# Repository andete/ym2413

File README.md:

ym2413
======

openMSX YM2413 reverse engineering project

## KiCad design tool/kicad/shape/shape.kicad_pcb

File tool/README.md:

Edit the efm32gg332f1024_pinout.edc file with simplicity studio.

Find it here: http://community.silabs.com/t5/Simplicity-Studio-and-Software/Simplicity-Studio-1-20-energyAware-Tools-OSX-Linux/m-p/107821#M8497

Download the GCC toolchain from:

https://launchpad.net/gcc-arm-embedded/+download

and set the LINUXCS environment var to point to it.

see also: 

http://joost.damad.be/2013/11/using-efm32-simplicitystudio-under-linux.html

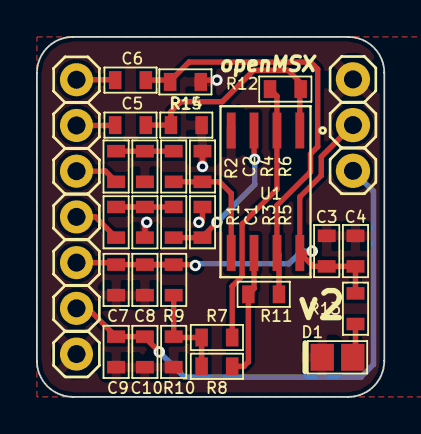
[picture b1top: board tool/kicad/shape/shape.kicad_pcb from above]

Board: 2 copper layers, 19.3 x 20.0 mm, 29 parts (0 on the bottom side), 17 nets.

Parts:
C1, C2: 2.2nF; 0603_S
C3: 0.1uF; 0603_S
C4, C7, C9: 1uF; 0603_S
C5, C6: 0Ohm; 0603_S
C8, C10: 1nF; 0603_S
D1: LED; 0805_LED
K1: CONN_3; PIN_1X3
P1: CONN_7; PIN_1X7_S
R1, R2: 0/2.2k; 0603_S_R
R3, R4, R7, R8: 68k; 0603_S_R
R5, R6, R11, R12: 100k; 0603_S_R
R9: 1.5k; 0603_S_R
R10: 1.21k; 0603_S_R
R13: 3k3; 0603_S_R
R14, R15: NC; 0603_S_R
U1: MCP6022; ATMEL_SO8

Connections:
+3.3V: C9.2, C10.2, K1.3, P1.2
+5V: C3.2, C4.2, C7.2, C8.2, K1.2, P1.3, R9.2, R13.2, U1.8
/MO: P1.4, R1.1
/MOA: C1.1, R1.2, R3.1
/MOB: R3.2, R5.1, U1.3
/MOO: C5.1, R12.1, R14.2, U1.1
/MO_SAMPLE: C5.2, P1.6
/RO: P1.5, R2.1
/ROA: C2.1, R2.2, R4.1
/ROB: R4.2, R6.1, U1.5
/ROO: C6.1, R11.1, R15.1, U1.7
/RO_SAMPLE: C6.2, P1.7
/VREF: R7.1, R8.1, R9.1, R10.2
GND: C1.2, C2.2, C3.1, C4.1, C7.1, C8.1, C9.1, C10.1, D1.2, K1.1, P1.1, R5.2, R6.2, R10.1, R14.1, R15.2, U1.4
unnamed: D1.1, R13.1
unnamed: R8.2, R11.2, U1.6
unnamed: R7.2, R12.2, U1.2

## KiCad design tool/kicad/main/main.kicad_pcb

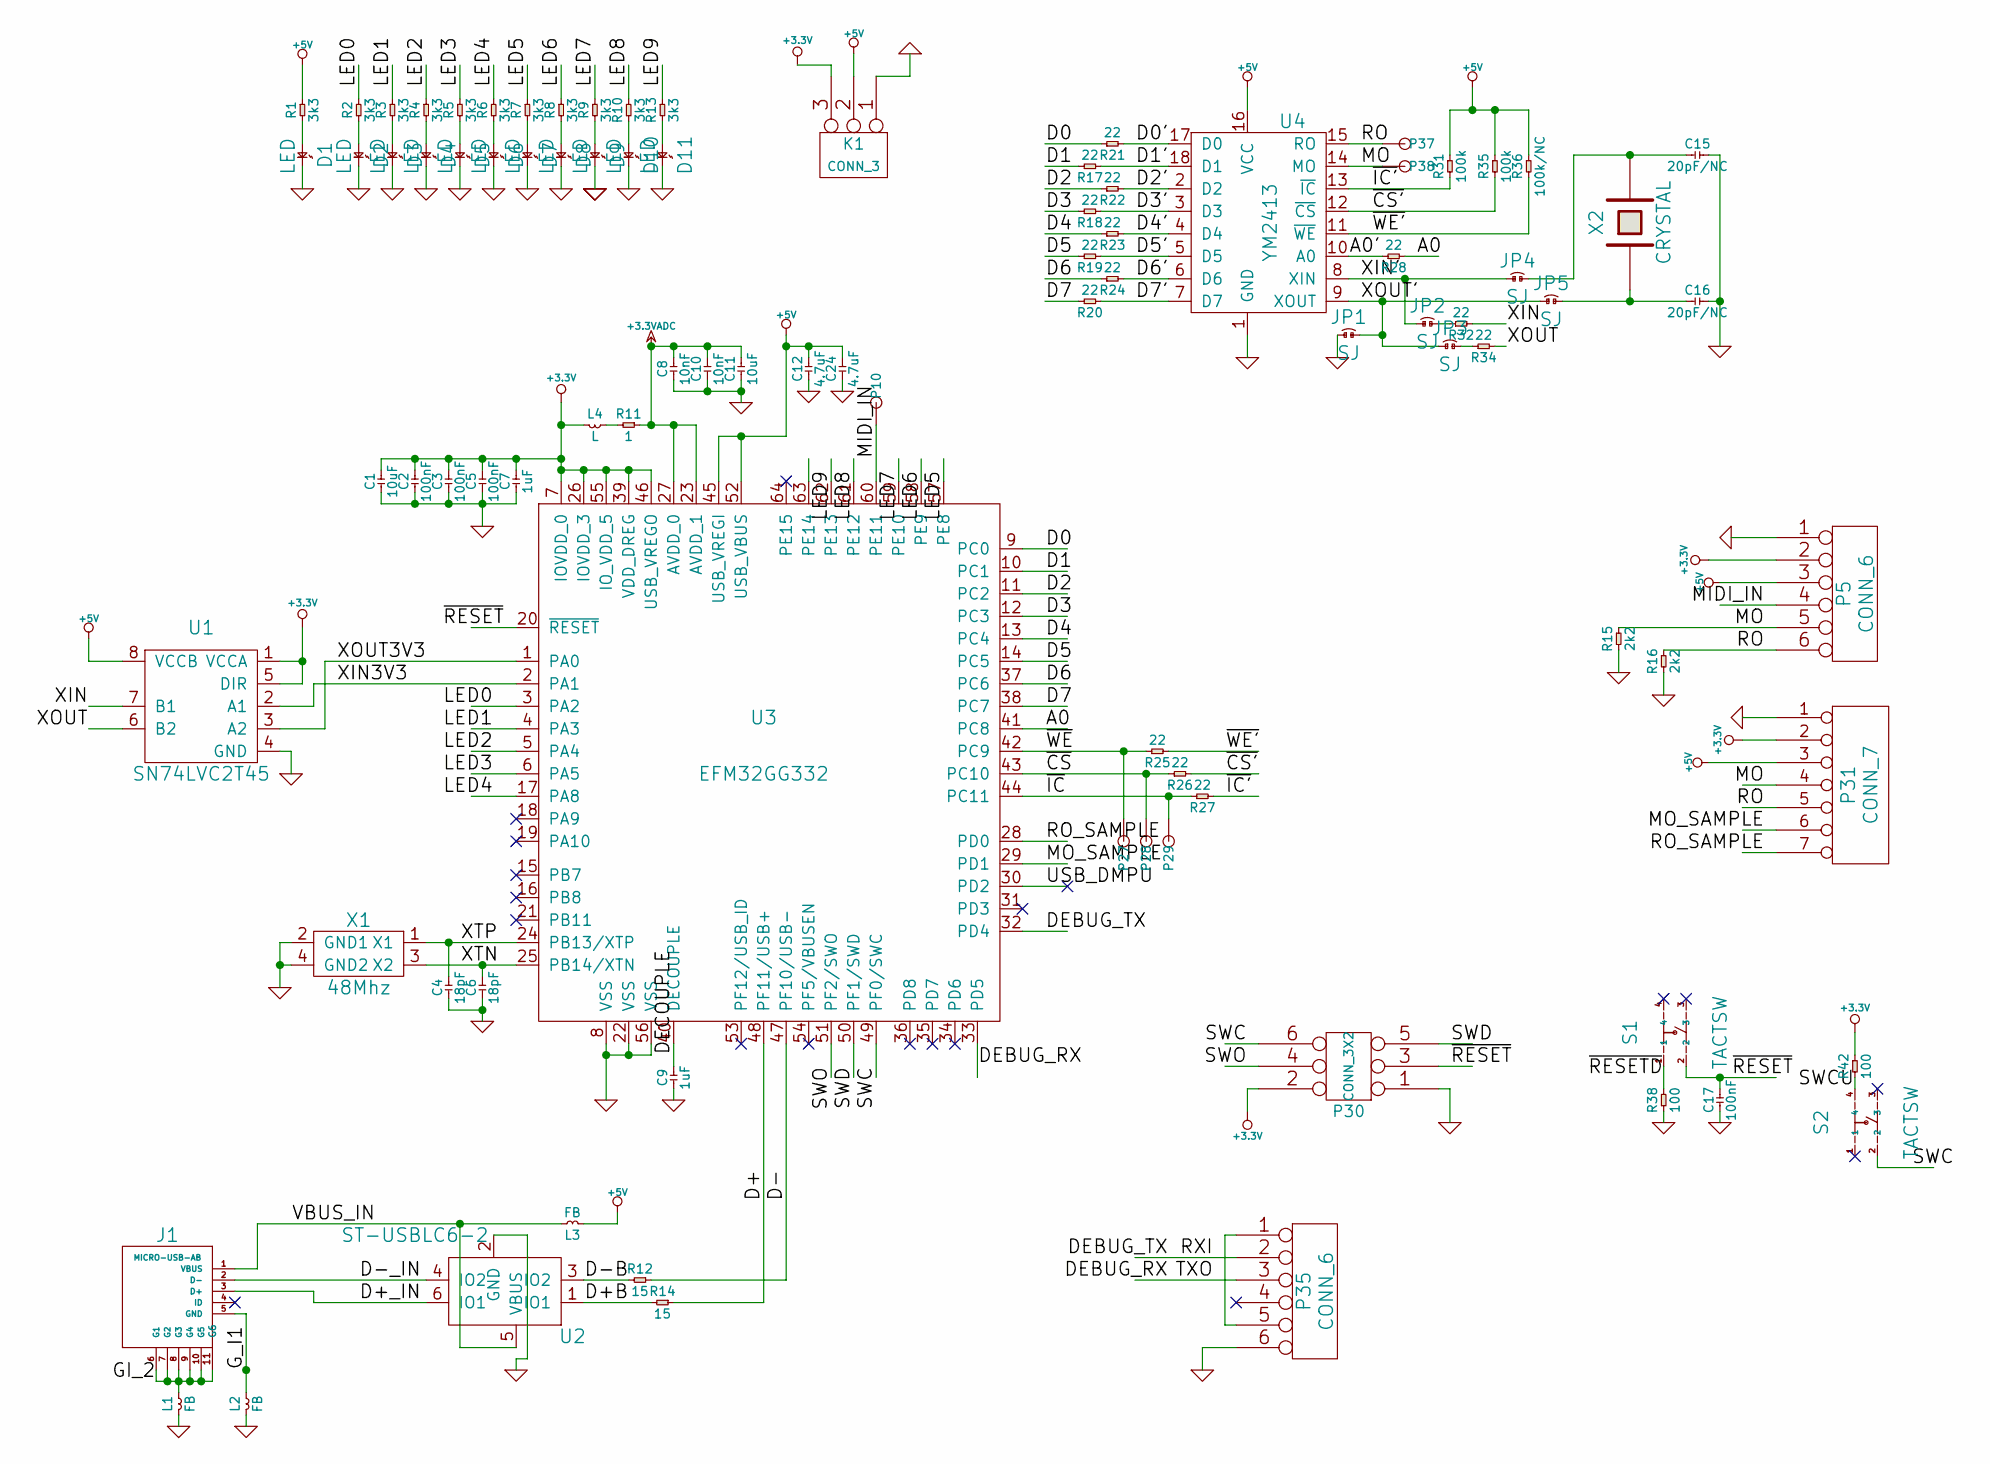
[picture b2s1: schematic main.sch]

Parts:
C1, C11: 10uF
C2, C3, C5, C17: 100nF
C4, C6: 18pF
C7, C9: 1uF
C8, C10: 10nF
C12, C24: 4.7uF
C15, C16: 20pF/NC
D1, D2, D3, D4, D5, D6, D7, D8, D9, D10, D11: LED
J1: MICRO-USB-AB
JP1, JP2, JP3, JP4, JP5: SJ
K1: CONN_3
L1, L2, L3: FB
L4: L
P5, P35: CONN_6
P10, P27, P28, P29, P37, P38: TEST_POINT
P30: CONN_3X2
P31: CONN_7
R1, R2, R3, R4, R5, R6, R7, R8, R9, R10, R13: 3k3
R11: 1
R12, R14: 15
R15, R16: 2k2
R17, R18, R19, R20, R21, R22, R23, R24, R25, R26, R27, R28, R32, R34: 22
R31, R35: 100k
R36: 100k/NC
R38, R42: 100
S1, S2: TACTSW
U1: SN74LVC2T45
U2: ST-USBLC6-2
U3: EFM32GG332
U4: YM2413
X1: 48Mhz
X2: CRYSTAL

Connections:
+3.3V: C1.2, C2.2, C3.2, C5.2, C7.2, K1.3, L4.1, P5.2, P30.2, P31.2, R42.2, U1.1 (VCCA), U1.5 (DIR), U3.7 (IOVDD_0), U3.26 (IOVDD_3), U3.39 (VDD_DREG), U3.46 (USB_VREGO), U3.55 (IO_VDD_5)
+3.3VADC: C8.2, C10.2, C11.2, R11.2, U3.23 (AVDD_1), U3.27 (AVDD_0)
+5V: C12.2, C24.2, K1.2 (PM), L3.1, P5.3, P31.3, R1.2, R31.2, R35.2, R36.2, U1.8 (VCCB), U3.45 (USB_VREGI), U3.52 (USB_VBUS), U4.16 (VCC)
/A0: R28.1, U3.41 (PC8)
/A0': R28.2, U4.10 (A0)
/D0: R21.2, U3.9 (PC0)
/D0': R21.1, U4.17 (D0)
/D1: R17.2, U3.10 (PC1)
/D1': R17.1, U4.18 (D1)
/D2: R22.2, U3.11 (PC2)
/D2': R22.1, U4.2 (D2)
/D3: R18.2, U3.12 (PC3)
/D3': R18.1, U4.3 (D3)
/D4: R23.2, U3.13 (PC4)
/D4': R23.1, U4.4 (D4)
/D5: R19.2, U3.14 (PC5)
/D5': R19.1, U4.5 (D5)
/D6: R24.2, U3.37 (PC6)
/D6': R24.1, U4.6 (D6)
/D7: R20.2, U3.38 (PC7)
/D7': R20.1, U4.7 (D7)
/D+: R14.2, U3.48 (PF11/USB+)
/D+B: R14.1, U2.1 (IO1)
/D+_IN: J1.3 (D+), U2.6 (IO1)
/D-: R12.2, U3.47 (PF10/USB-)
/D-B: R12.1, U2.3 (IO2)
/D-_IN: J1.2 (D-), U2.4 (IO2)
/DEBUG_RX: P35.3, U3.33 (PD5)
/DEBUG_TX: P35.2, U3.32 (PD4)
/DECOUPLE: C9.2, U3.40 (DECOUPLE)
/GI_2: J1.6 (G1), J1.7 (G2), J1.8 (G3), J1.9 (G4), J1.10 (G5), J1.11 (G6), L1.2
/G_I1: J1.5 (GND), L2.2
/LED0: R2.2, U3.3 (PA2)
/LED1: R3.2, U3.4 (PA3)
/LED2: R4.2, U3.5 (PA4)
/LED3: R5.2, U3.6 (PA5)
/LED4: R6.2, U3.17 (PA8)
/LED5: R7.2, U3.57 (PE8)
/LED6: R8.2, U3.58 (PE9)
/LED7: R9.2, U3.59 (PE10)
/LED8: R10.2, U3.61 (PE12)
/LED9: R13.2, U3.62 (PE13)
/MIDI_IN: P5.4, P10.1, U3.60 (PE11)
/MO: P5.5, P31.4, P38.1, R15.2, U4.14 (MO)
/MO_SAMPLE: P31.6, U3.29 (PD1)
/RO: P5.6, P31.5, P37.1, R16.2, U4.15 (RO)
/RO_SAMPLE: P31.7, U3.28 (PD0)
/SWC: P30.6, S2.2, U3.49 (PF0/SWC)
/SWCU: R42.1, S2.4
/SWD: P30.5, U3.50 (PF1/SWD)
/SWO: P30.4, U3.51 (PF2/SWO)
/USB_DMPU: U3.30 (PD2)
/VBUS_IN: J1.1 (VBUS), L3.2, U2.5 (VBUS)
/XIN: R32.1, U1.7 (B1)
/XIN3V3: U1.2 (A1), U3.2 (PA1)
/XIN': JP2.1, JP4.1, U4.8 (XIN)
/XOUT: R34.1, U1.6 (B2)
/XOUT3V3: U1.3 (A2), U3.1 (PA0)
/XOUT': JP1.2, JP3.1, JP5.1, U4.9 (XOUT)
/XTN: C6.2, U3.25 (PB14/XTN), X1.3 (X2)
/XTP: C4.2, U3.24 (PB13/XTP), X1.1 (X1)
/~CS: P28.1, R26.2, U3.43 (PC10)
/~CS': R26.1, R35.1, U4.12 (~CS)
/~IC: P29.1, R27.2, U3.44 (PC11)
/~IC': R27.1, R31.1, U4.13 (~IC)
/~RESET: C17.2, P30.3, S1.2, U3.20 (~RESET)
/~RESETD: R38.2, S1.1
/~WE: P27.1, R25.2, U3.42 (PC9)
/~WE': R25.1, R36.1, U4.11 (~WE)
GND: C1.1, C2.1, C3.1, C4.1, C5.1, C6.1, C7.1, C8.1, C9.1, C10.1, C11.1, C12.1, C15.2, C16.2, C17.1, C24.1, D1.2, D2.2, D3.2, D4.2, D5.2, D6.2, D7.2, D8.2, D9.2, D10.2, D11.2, JP1.1, K1.1, L1.1, L2.1, P5.1, P30.1, P31.1, P35.6, R15.1, R16.1, R38.1, U1.4 (GND), U2.2 (GND), U3.8 (VSS), U3.22 (VSS), U3.56 (VSS), U4.1 (GND), X1.2 (GND1), X1.4 (GND2)
unnamed: C15.1, JP4.2, X2.2
unnamed: C16.1, JP5.2, X2.1
unnamed: D1.1, R1.1
unnamed: D2.1, R2.1
unnamed: D3.1, R3.1
unnamed: D4.1, R4.1
unnamed: D5.1, R5.1
unnamed: D6.1, R6.1
unnamed: D7.1, R7.1
unnamed: D8.1, R8.1
unnamed: D9.1, R9.1
unnamed: D10.1, R10.1
unnamed: D11.1, R13.1
unnamed: JP2.2, R32.2
unnamed: JP3.2, R34.2
unnamed: L4.2, R11.1
unnamed: P35.1, P35.5

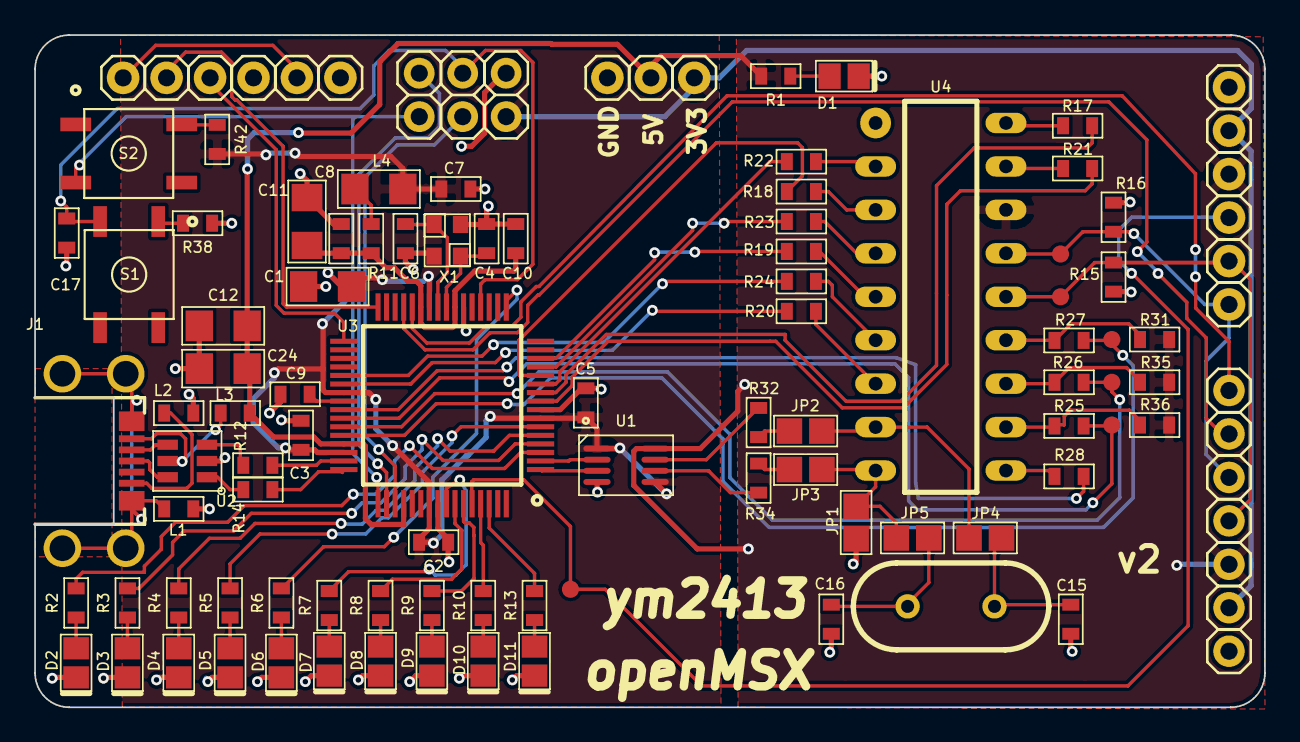
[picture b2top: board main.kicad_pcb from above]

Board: 2 copper layers, 71.9 x 39.3 mm, 91 parts (0 on the bottom side), 86 nets.

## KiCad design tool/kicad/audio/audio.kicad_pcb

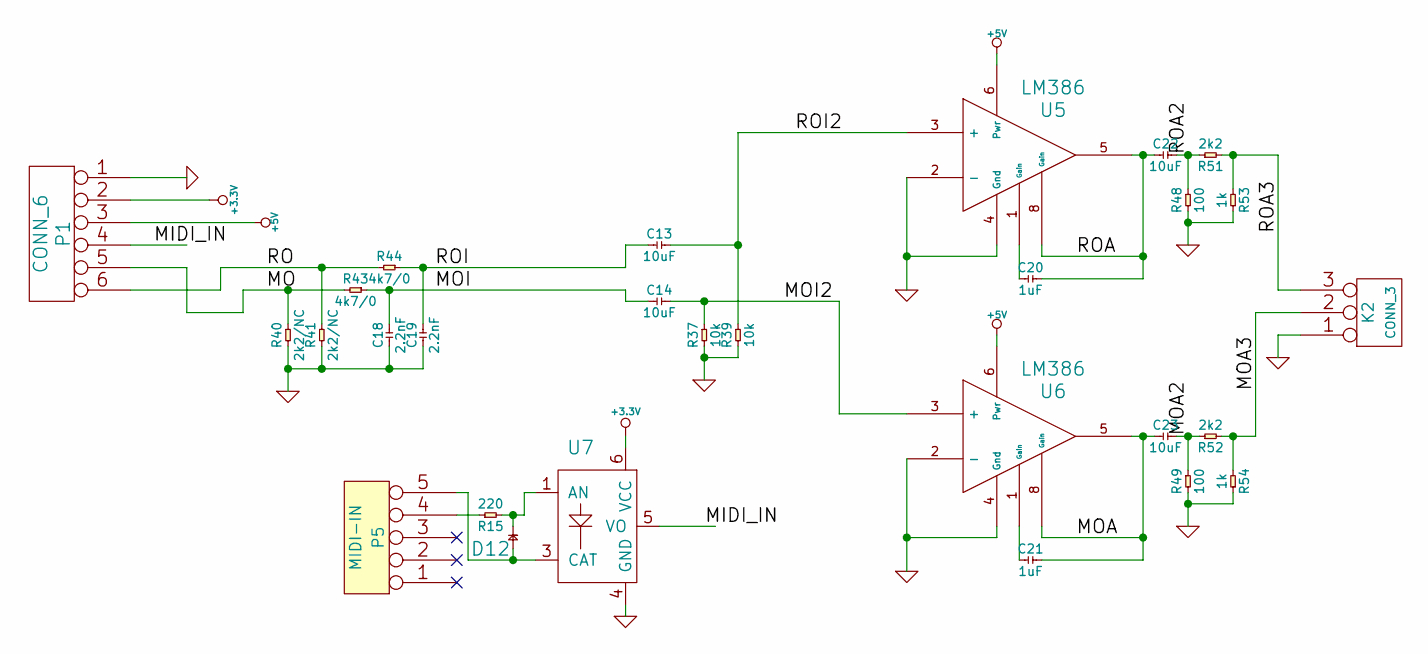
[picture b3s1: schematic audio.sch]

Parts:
C13, C14, C22, C23: 10uF
C18, C19: 2.2nF
C20, C21: 1uF
D12: D
K2: CONN_3
P1: CONN_6
P5: MIDI-IN
R15: 220
R37, R39: 10k
R40, R41: 2k2/NC
R43, R44: 4k7/0
R48, R49: 100
R51, R52: 2k2
R53, R54: 1k
U5, U6: LM386
U7: ACPL-M21L

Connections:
+3.3V: P1.2, U7.6 (VCC)
+5V: P1.3, U5.6 (Pwr), U6.6 (Pwr)
/MIDI_IN: P1.4, U7.5 (VO)
/MO: P1.5, R40.2, R43.1
/MOA: C21.2, C23.1, U6.5, U6.8 (Gain)
/MOA2: C23.2, R49.2, R52.2
/MOA3: K2.2 (PM), R52.1, R54.1
/MOI: C14.1, C18.2, R43.2
/MOI2: C14.2, R37.2, U6.3 (+)
/RO: P1.6, R41.2, R44.1
/ROA: C20.2, C22.1, U5.5, U5.8 (Gain)
/ROA2: C22.2, R48.2, R51.2
/ROA3: K2.3, R51.1, R53.1
/ROI: C13.1, C19.2, R44.2
/ROI2: C13.2, R39.2, U5.3 (+)
GND: C18.1, C19.1, K2.1, P1.1, R37.1, R39.1, R40.1, R41.1, R48.1, R49.1, R53.2, R54.2, U5.2 (-), U5.4 (Gnd), U6.2 (-), U6.4 (Gnd), U7.4 (GND)
unnamed: C20.1, U5.1 (Gain)
unnamed: C21.1, U6.1 (Gain)
unnamed: D12.1, P5.5, U7.3 (CAT)
unnamed: D12.2, R15.1, U7.1 (AN)
unnamed: P5.4, R15.2

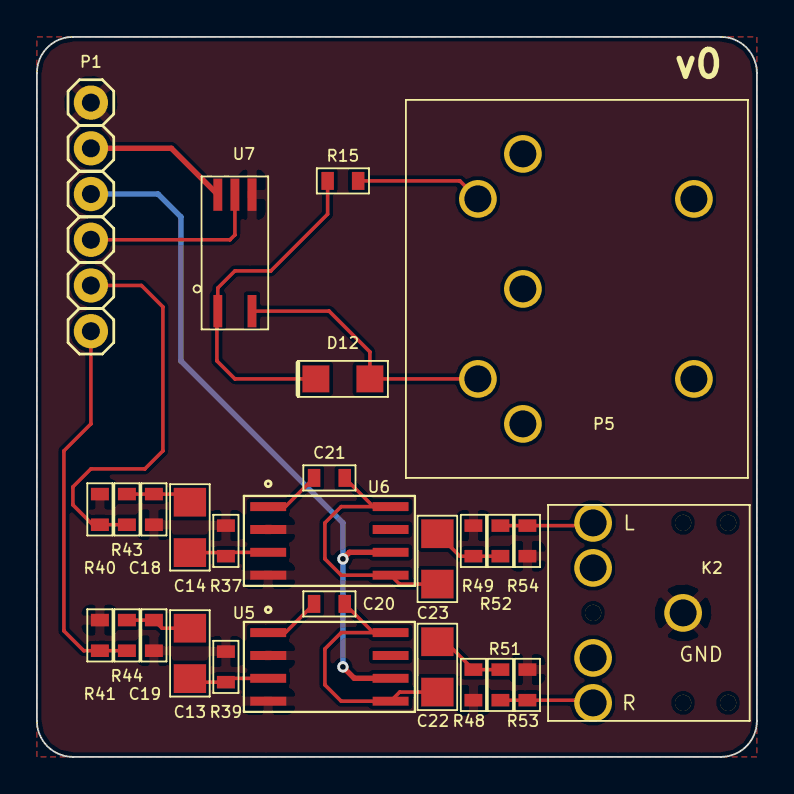
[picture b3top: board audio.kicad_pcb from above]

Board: 2 copper layers, 40.0 x 40.0 mm, 28 parts (0 on the bottom side), 21 nets.

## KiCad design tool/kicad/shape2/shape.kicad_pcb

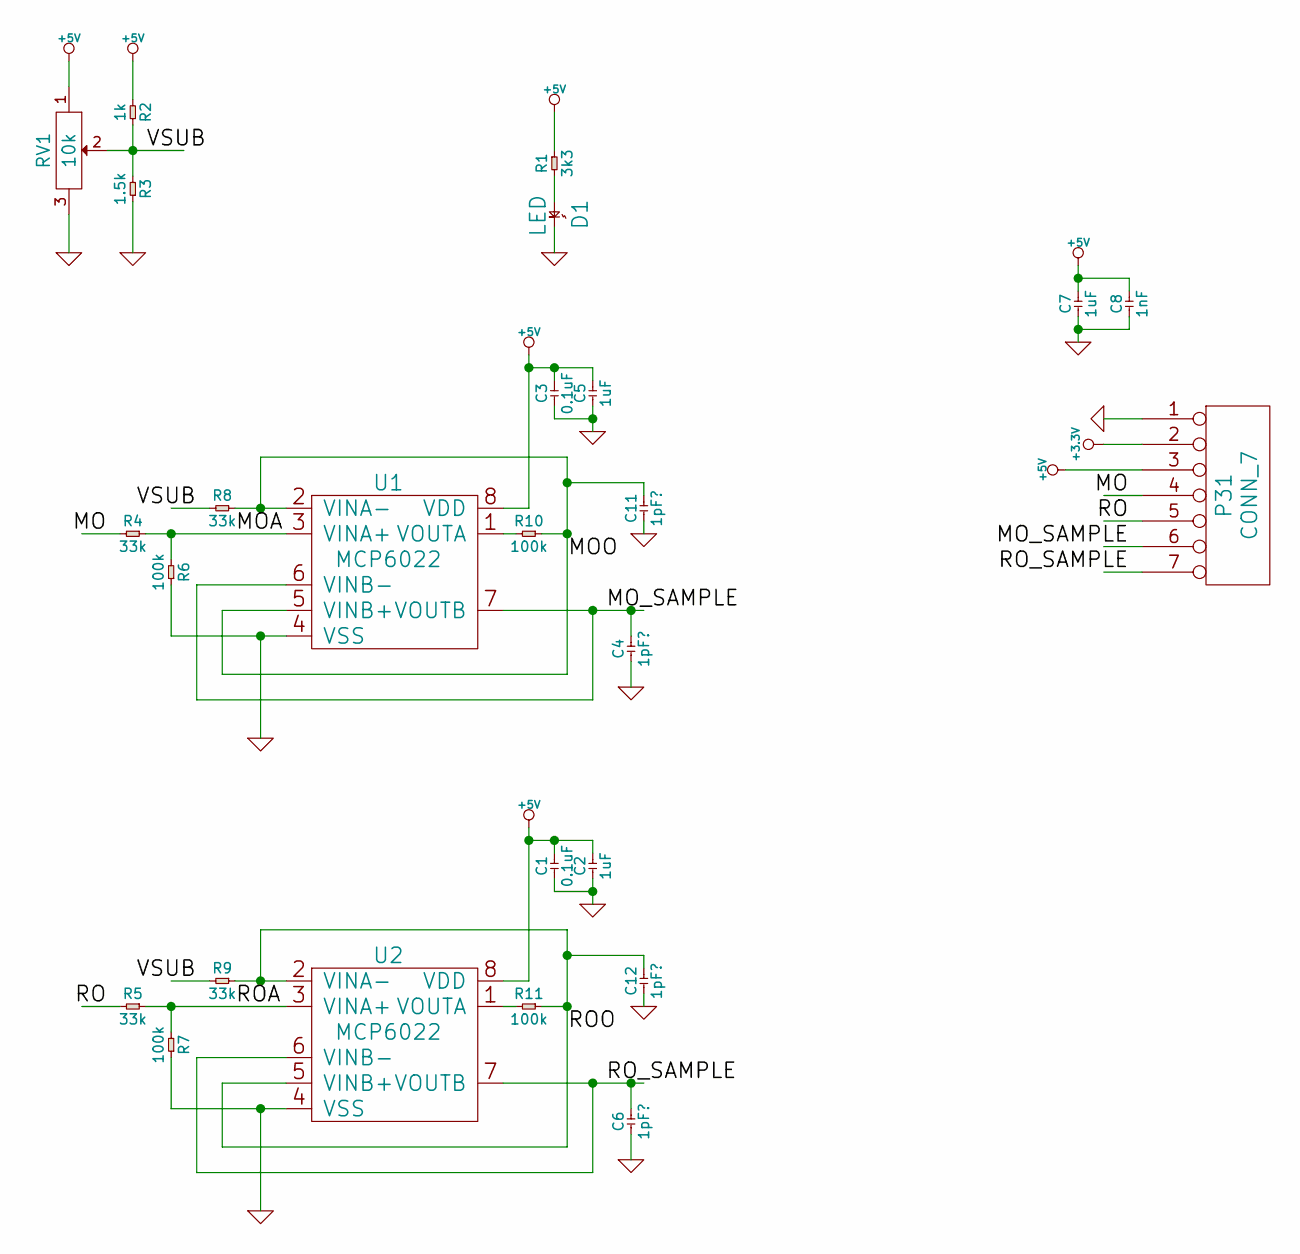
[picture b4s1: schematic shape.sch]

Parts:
C1, C3: 0.1uF
C2, C5, C7: 1uF
C4, C6, C11, C12: 1pF?
C8: 1nF
D1: LED
P31: CONN_7
R1: 3k3
R2: 1k
R3: 1.5k
R4, R5, R8, R9: 33k
R6, R7, R10, R11: 100k
RV1: 10k
U1, U2: MCP6022

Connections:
+3.3V: P31.2
+5V: C1.2, C2.2, C3.2, C5.2, C7.2, C8.2, P31.3, R1.2, R2.1, RV1.1, U1.8 (VDD), U2.8 (VDD)
/MO: P31.4, R4.1
/MOA: R4.2, R6.1, U1.3 (VINA+)
/MOO: C11.2, R8.2, R10.2, U1.2 (VINA-), U1.5 (VINB+)
/MO_SAMPLE: C4.2, P31.6, U1.6 (VINB-), U1.7 (VOUTB)
/RO: P31.5, R5.1
/ROA: R5.2, R7.1, U2.3 (VINA+)
/ROO: C12.2, R9.2, R11.2, U2.2 (VINA-), U2.5 (VINB+)
/RO_SAMPLE: C6.2, P31.7, U2.6 (VINB-), U2.7 (VOUTB)
/VSUB: R2.2, R3.1, R8.1, R9.1, RV1.2
GND: C1.1, C2.1, C3.1, C4.1, C5.1, C6.1, C7.1, C8.1, C11.1, C12.1, D1.2, P31.1, R3.2, R6.2, R7.2, RV1.3, U1.4 (VSS), U2.4 (VSS)
unnamed: D1.1, R1.1
unnamed: R10.1, U1.1 (VOUTA)
unnamed: R11.1, U2.1 (VOUTA)

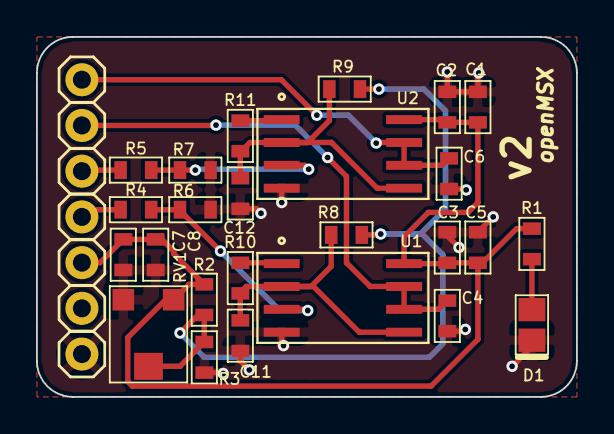
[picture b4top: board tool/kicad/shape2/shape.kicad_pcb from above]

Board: 2 copper layers, 30.0 x 20.0 mm, 26 parts (0 on the bottom side), 14 nets.

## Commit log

2014-02-05 add specs
2014-02-05 add specs for micro
2014-02-05 move to tool subdir
2014-02-05 basic pinout (unfinished)
2014-02-05 expecting to be using this xtal
2014-02-05 document the pinout file tool
2014-02-05 add link to blog post
2014-02-05 add basic board draft
2014-02-05 add 3.5Mhz crystal spec
2014-02-05 add energy micro utility files
2014-02-05 add toolchain files
2014-02-05 add CMSIS includes
2014-02-05 add common files
2014-02-05 fix Makefile
2014-02-05 add pointer to toolchain
2014-02-05 remove --specs=nano.specs
2014-02-06 add specific footprints
2014-02-06 add EFM32 to sch
2014-02-06 add basic mcu perif
2014-02-07 add 48Mhz xtal; add usb hardware design guidelines
2014-02-07 create USB power circuitry and hook up USB power to efm32
2014-02-07 hook up usb- and usb+
2014-02-09 add fm-pak docu
2014-02-09 add optional audio amplifier output circuitry
2014-02-09 add optocoupled midi in
2014-02-09 add midi protection diode
2014-02-09 add extra solder jumpers for XIN/XOUT handling on YM
2014-02-09 add SWC pull-up button to enable bootloader programming
2014-02-09 add fast lvl shifer IC to make sure we provide a 5V clock on XI
2014-02-09 cleanup; assign pins; add test points; restart pcb layout from zero
2014-02-10 add 6-pin FTDI debug header
2014-02-10 rough layout
2014-02-10 slightly tighen layout
2014-02-10 fix used optocoupler
2014-02-10 add spec for optocoupler
2014-02-13 latest
2014-02-14 add pinout as pdf
2014-02-14 add tick & delay
2014-02-14 add spec for audio out socket
2014-02-14 clock enables
2014-02-14 add adc setup
2014-02-14 add leuart0
2014-02-14 add timer0
2014-02-14 add swd/swo
2014-02-14 add usart0
2014-02-14 and add file
2014-02-14 add usb
2014-02-14 move timer pin init to timer0.h, although it is probably incorrect for what we want
2014-02-14 add dma
2014-02-14 leuart0 more DMA setup
2014-02-14 wrap up leuart0 receive DMA
2014-02-14 add led code
2014-02-14 basic ym pin setup
2014-02-14 make pinout more clear
2014-02-14 add windows CDC .inf file cause windows needs it even for generic USB serial devices
2014-02-14 add usb stack
2014-02-14 USB stuff (WIP)
2014-02-14 fix compilation with C++11
2014-02-15 rename ush.h -> usbcdc.h
2014-02-15 more usb skeleton code
2014-02-15 compile in USB stack c files
2014-02-15 more usbcdc work, print Hello world on usbcdc interface
2014-02-15 fixed build
2014-02-16 add timer0 skeleton
2014-02-16 timer work
2014-02-16 set freq at clock start
2014-02-16 move timer init code to timer0.h, rename all header files to .hh to make clear they are C++
2014-02-16 add remark about adding more direct IO access
2014-02-16 document PWM duty cycle
2014-02-17 add din5 midi connector spec
2014-02-17 add midi and audio connector footprints
2014-02-17 fix audio footprint; add to board
2014-02-20 ERC fixes
2014-02-20 work on 3V3 part
2014-02-20 more layout work
2014-02-21 sync
2014-02-21 route some of the LEDs
2014-02-21 finish first layout
2014-02-21 re-add second 5 LEDs, but hook up to more reachable ports
2014-02-21 wrap up silks
2014-02-21 cleanup
2014-02-21 add openMSX to bottom as well
2014-02-22 add usbconfig.h
2014-02-22 small tweak to allow using a different LINUXCS
2014-02-22 Early version of test program
    The test program can be compiled in two mode (for now using two different
    Makefiles).
    - Makefile: to control the actual hardware
    - Makefile.virtual: to control virtual hardware
    The second version can be run on a regular (desktop) machine. It contains
    some rough checks about the way how the YM2413 pins are used. It also prints
2014-05-31 fix D+ and D- in schematic
2014-05-31 fix USB pin swap in board
2014-05-31 modify linker script to accomodate having a bootloader
2014-05-31 use programmer again for upload; led blink demo
2014-07-01 add pretty files
2014-07-01 remove logos
2014-07-01 add fp-lib-table file with pretty ref
2014-07-13 use pretty for footprints
2014-07-13 move old _dev board to subdirectory
2014-07-13 create derived audio board from _dev board
2014-07-13 fix and layout audio/midi board
2014-07-13 add silk to bottom to please oshpark
2014-07-13 create main kicad prj copied from _dev
2014-07-13 cleanup schematic
2014-07-13 update solder jumpers
2014-07-13 adapt audio to don't have the 2k2s on this board by default
2014-07-13 annotation
2014-07-13 rework main pcb
2014-08-03 main board WIP
2014-08-03 base shape board on main
2014-08-03 add opamp spec, cleanup shape board
2014-08-03 shape board schematic
2014-08-03 finish shape pcb
2014-08-03 use new prefered USB-B connector
2014-08-03 main layout (WIP)
2014-08-03 more main board work
2014-08-03 main finish rough layout
2014-08-03 updated main board
2014-08-11 shaper 2
2014-08-11 layout
2014-08-25 store
2014-08-25 updated shaper board design (tested in breadboard)
2014-08-26 update footprints
2014-08-26 fix main USB connector
2014-11-16 support xmodem based FW upload using screen; use linker script that keeps bootloader intact
2014-11-16 comments in Makefile; updated bootloader (blinks during transfer)
2014-11-16 fix quoting
2014-12-05 add board.hh
2014-12-06 remove obsolete 'shape2'
2014-12-09 Added tool2 subdirectory
    For the moment this is still very close to the 'tool' subdir. I made a copy
    instead of modifying that dir so that I always have a working fallback in case
    I screw something up.
    The only real change so far is that I split the various '.hh' files in 'actual'
    header and implementation files (.hh + .cc). (Before it were actually also
    implementation files that were #included in main.cc).
2014-12-09 Initial experiments using ADC
    Not yet synchronized with the YM2413 clock.
2014-12-09 More efficient YM2413 access
    - Write 12 pins at once instead of pin-per-pin
    - Added timer0::busyWaitN() to wait for N YM2413 clock cycles (instead of
    waiting for N milliseconds).
2014-12-11 Synchronize ADC with YM2413 clock
    We now take one sample per YM2413 clock.
    Next step is to take one sample every 72 YM2413 clocks, but I coudn't get that
    working yet.
2014-12-13 Much more stable ADC measurements
    - Use differential ADC mode (RO-MO instead of MO)
    - Get Timer1 to work (USB code was using the same timer, moved that to timer3)
2014-12-20 use DMA to send continuous stream of samples to host
2014-12-20 Proper synchronization of timer-1
    Timer-1 determines which of the 72 samples in the YM2413 period we sample.
    Before we used a hack to sync this. And that hack only worked after resetting
    the board, not after reprogramming and then running the program (without
    reset).
    Now we have a routine that properly detects the position of music channel 1 and
    synchronizes timer-1 to that position.
2014-12-26 added USB callback
2014-12-26 event loop
2014-12-26 added play script
2014-12-26 move towards an IRQ driven main loop
2014-12-26 small tweaks
2014-12-26 added callibrateOffset()
2014-12-29 receiving data over USB works now (and is integrated in the main event handling loop)
2015-01-11 tune shape board
2015-02-09 Mapping ADC samples to YM2413 values
2015-03-05 More dynamic firmware / calibration tool
    Made the firmware more dynamic, meaning that we don't need to reflash a new
    program each time we want to test a different thing. Instead we can now send
    instructions over USB (like write YM2413 registers or start/stop capturing).
    Also added a tool 'calibrate' that uses this new firmware to capture a sine
    wave and based on this calculates the positions of the YM2413 output levels.
2015-03-06 Started to write 20150305.txt, still WIP
2015-03-06 more or less finished 20150305.txt
2015-03-11 WIP: analyze volume levels
2015-03-12 forgot to add 20150311.txt, made some tweaks but still WIP
2015-03-13 more tweaks
2015-03-16 WIP: record (some) frequency measurements ... seems like phase-counter is {10,9} bits fixed-point
2015-03-17 explain phase-counter, still WIP
2015-03-17 finished post about phase-counters
2015-03-19 WIP: envelope generator - decay rate
2015-03-20 WIP: EG updates, still need to confirm with more measurements
2015-03-22 finished post about EG-decay
2015-03-26 wip: early version of attack-rates
2015-04-02 wip: exp attack tools
2015-04-06 wip: attack rates
2015-04-07 update, still wip
2015-04-07 final tweaks
2015-04-11 WIP: log/sin tables
2015-04-11 finish log/sin table post
2015-11-28 wrote post about AM
2015-12-01 Added post about FM
2015-12-03 wip: added some graphs for modulator+carrier
2015-12-07 wip: post about mod-car connection
2015-12-08 some updates (still wip)
2015-12-09 final(?) tweaks
2015-12-12 created post about the feedback function
2015-12-17 added post about registers / ksl
2015-12-24 finished post about SL and KSR
2015-12-26 update tool with writeRegisterDelay() / increase buffer to hold script
2015-12-31 investigated envelopes in more detail
2015-12-31 forgot to remove 'DRAFT'
2016-01-02 two small fixes, thanks Grauw, Manuel for reviewing
2016-02-10 post about adsr transitions
2016-07-19 Initial model / investigate 'small' signals
2017-01-26 new post about the ym2413 attack curve, draft version
2017-01-27 final(?) tweaks in attack.txt
2018-05-13 Added article about LFSR
2019-12-31 Added article about rhythm sounds
2020-01-02 some fixes after feedback from Nuke.YKT
2020-01-02 Document the difference between the LFSR we found and the one that's used by Nuke.YKT
2020-01-02 update regarding noise bit
2020-05-01 more consistent naming in formulas
